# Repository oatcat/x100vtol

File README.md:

# x100vtol
a 100mm 4-rotor small drone using brushed motors, 2s li-po battery, 60mm prop.
One piece PCB-as-chassic, onboard mosfet motor driver, GY-86 as IMU.
Uses taulabs software. Hardware compatible as DISOVERY F4.

## To make one:
Order the PCB from a fab house, buy the necessary parts, solder the PCB.
Connect a S.BUS reciever to the port and fix the reciever on the PCB.
Flash taulabs firmware using ST-LINK, configure the UAV.

## BOM

Apart from the PCB BOM, you will need to secure the motors onto the PCB.
The motor mount I used is bought on taobao.com. If you can't get one you can change the PCB to suit your motor mount.

A small FPV Camera with built in VTX is needed if FPV is desireable.

A ~550mAh 2S battery is needed, and you will need a strap to fix the battery.
There are 2 slots on the PCB you can use to strap the battery.

For proper takeoff and landing you will need some kind of landing gear.
Just glue a small piece of plastic under each motor mount will be fine.

To flash the STM32 you will need ST-Link. Either a standalone one or a builtin on the Discovery board will be fine.

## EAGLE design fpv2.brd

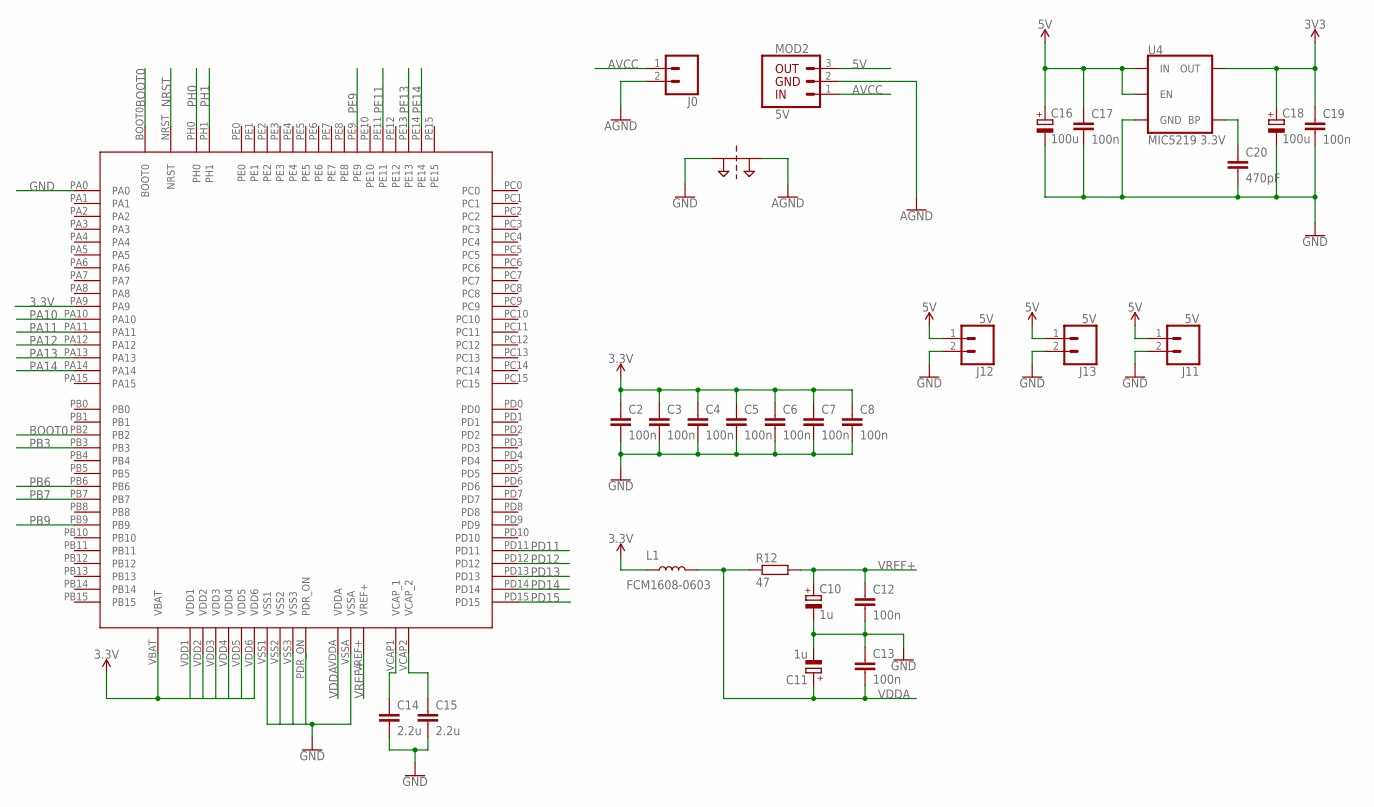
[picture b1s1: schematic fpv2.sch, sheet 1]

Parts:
C2, C3, C4, C5, C6, C7, C8, C12, C13, C17, C19: 100n; C0603
C10, C11: 1u; A/3216-18R
C14, C15: 2.2u; C1206
C16, C18: 100u; SMC_B
C20: 470pF; C0603
J0: CONN_02LOCK_LONGPADS; 1X02_LOCK_LONGPADS
J11, J12, J13: 5V; SMD
L1: FCM1608-0603; 0603
MOD2: 5V; 1X03
R12: 47; R0603
SUPPLY1: 2PT_GND_TIE
U1: STM32F407VGT6; LQFP100
U4: MIC5219 3.3V; SOT23-5

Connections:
3.3V: C2.1, C3.1, C4.1, C5.1, C6.1, C7.1, C8.1, C18.+, C19.1, L1.1, U1.PA9, U1.VBAT, U1.VDD1, U1.VDD2, U1.VDD3, U1.VDD4, U1.VDD5, U1.VDD6, U4.5 (OUT); also elsewhere on the board
5V: C16.+, C17.1, J11.1, J12.1, J13.1, MOD2.3, U4.1 (IN), U4.3 (EN); also elsewhere on the board
AGND: J0.2, MOD2.2, SUPPLY1.P$2; also elsewhere on the board
AVCC: J0.1, MOD2.1; also elsewhere on the board
BOOT0: U1.BOOT0, U1.PB2; also elsewhere on the board
GND: C2.2, C3.2, C4.2, C5.2, C6.2, C7.2, C8.2, C10.-, C11.-, C12.2, C13.1, C14.2, C15.2, C16.-, C17.2, C18.-, C19.2, C20.2, J11.2, J12.2, J13.2, SUPPLY1.P$1, U1.PA0, U1.PDR_ON, U1.VSS1, U1.VSS2, U1.VSS3, U1.VSSA, U4.2 (GND); also elsewhere on the board
unnamed: C14.1, U1.VCAP1 (VCAP_1)
unnamed: C15.1, U1.VCAP2 (VCAP_2)
unnamed: C20.1, U4.4 (BP)
NRST: U1.NRST; also elsewhere on the board
PA10: U1.PA10
PA11: U1.PA11; also elsewhere on the board
PA12: U1.PA12; also elsewhere on the board
PA13: U1.PA13; also elsewhere on the board
PA14: U1.PA14; also elsewhere on the board
PB3: U1.PB3; also elsewhere on the board
PB6: U1.PB6; also elsewhere on the board
PB7: U1.PB7; also elsewhere on the board
PB9: U1.PB9; also elsewhere on the board
PD11: U1.PD11; also elsewhere on the board
PD12: U1.PD12; also elsewhere on the board
PD13: U1.PD13; also elsewhere on the board
PD14: U1.PD14; also elsewhere on the board
PD15: U1.PD15; also elsewhere on the board
PE9: U1.PE9; also elsewhere on the board
PE11: U1.PE11; also elsewhere on the board
PE13: U1.PE13; also elsewhere on the board
PE14: U1.PE14; also elsewhere on the board
PH0: U1.PH0; also elsewhere on the board
PH1: U1.PH1; also elsewhere on the board
VDDA: C11.+, C13.2, L1.2, R12.1, U1.VDDA
VREF+: C10.+, C12.1, R12.2, U1.VREF+

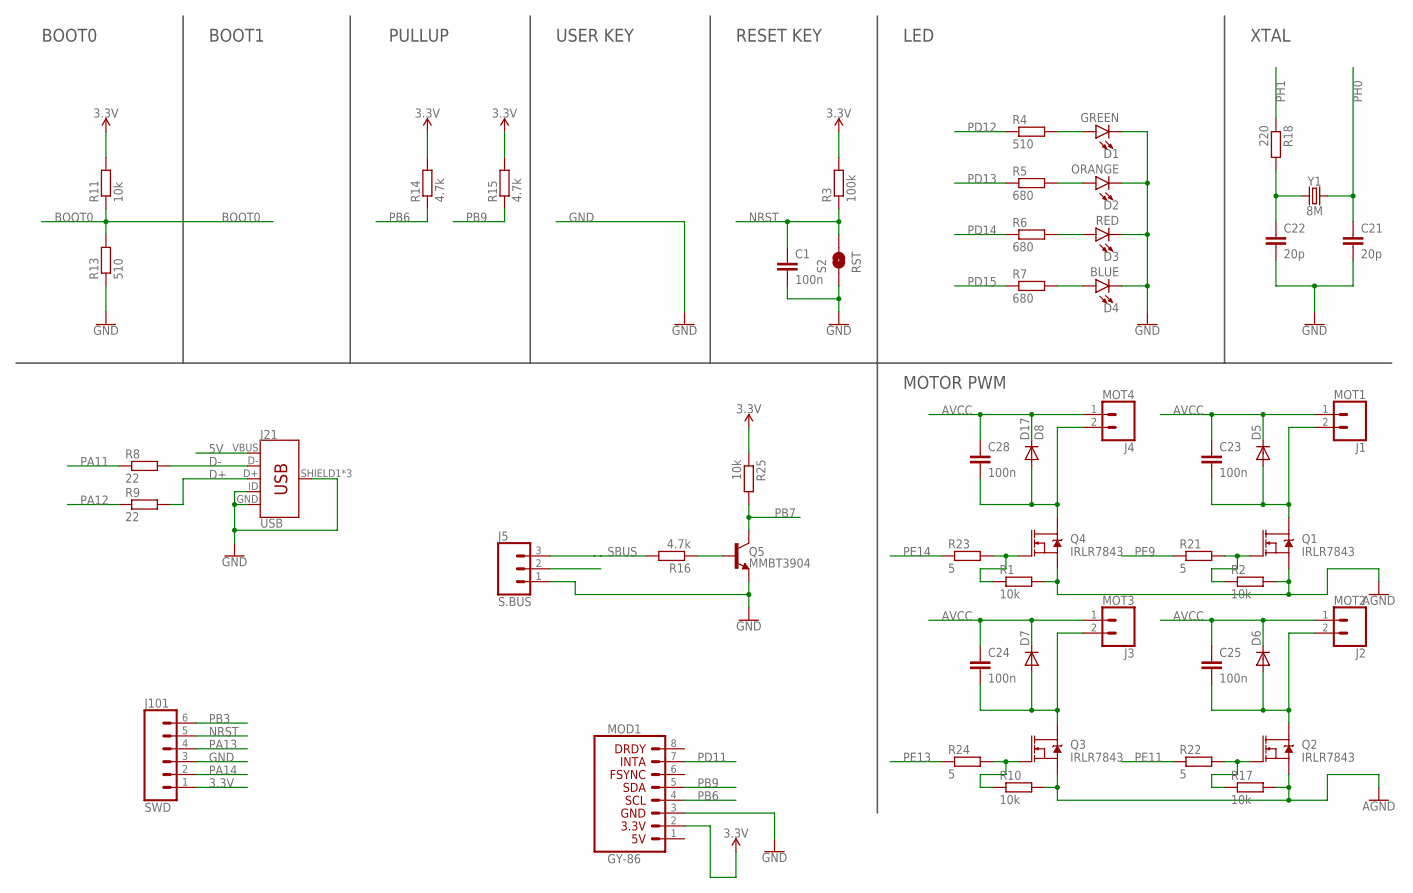
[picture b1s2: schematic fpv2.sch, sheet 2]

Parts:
C1, C23, C24, C25, C28: 100n; C0603
C21, C22: 20p; C0603
D1: GREEN; LED-0603
D2: ORANGE; LED-0603
D3: RED; LED-0603
D4: BLUE; LED-0603
D5, D6, D7: DIODE-DO214AC; DO214AC
D17: D8; DO214AC
J1: MOT1; 1X02_LOCK_LONGPADS
J2: MOT2; 1X02_LOCK_LONGPADS
J3: MOT3; 1X02_LOCK_LONGPADS
J4: MOT4; 1X02_LOCK_LONGPADS
J5: S.BUS; 1X03
J21: USB; USB-B-MICRO-SMD
J101: SWD; 1X06-SMD-FEMALE
MOD1: GY-86
Q1, Q2, Q3, Q4: IRLR7843; DPAK
Q5: MMBT3904; SOT23-3
R1, R2, R10, R11, R17, R25: 10k; R0603
R3: 100k; R0603
R4, R13: 510; R0603
R5, R6, R7: 680; R0603
R8, R9: 22; R0603
R14, R15, R16: 4.7k; R0603
R18: 220; R0603
R21, R22, R23, R24: 5; R0603
S2: RST; SMT-JUMPER_2_NO_NO-SILK
Y1: 8M; CRYSTAL-SMD-5X3.2-2PAD

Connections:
3.3V: J101.1, MOD1.2 (3.3V), R3.2, R11.2, R14.2, R15.2, R25.1; also elsewhere on the board
5V: J5.2, J21.VBUS; also elsewhere on the board
AGND: Q1.3 (S), Q2.3 (S), Q3.3 (S), Q4.3 (S), R1.2, R2.2, R10.2, R17.2; also elsewhere on the board
AVCC: C23.1, C24.1, C25.1, C28.1, D5.C, D6.C, D7.C, D17.C, J1.1, J2.1, J3.1, J4.1; also elsewhere on the board
BOOT0: R11.1, R13.2; also elsewhere on the board
D+: J21.D+, R9.2
D-: J21.D-, R8.2
GND: C1.2, C21.2, C22.2, D1.C, D2.C, D3.C, D4.C, J5.1, J21.GND, J21.ID, J21.SHIELD1 (SHIELD), J21.SHIELD2 (SHIELD), J21.SHIELD3 (SHIELD), J101.3, MOD1.3 (GND), Q5.2 (E), R13.1, S2.1; also elsewhere on the board
unnamed: C23.2, D5.A, J1.2, Q1.4 (D)
unnamed: D1.A, R4.2
unnamed: D2.A, R5.2
unnamed: D3.A, R6.2
unnamed: D4.A, R7.2
unnamed: C25.2, D6.A, J2.2, Q2.4 (D)
unnamed: Q4.1 (G), R1.1, R23.2
unnamed: Q1.1 (G), R2.1, R21.2
unnamed: C22.1, R18.2, Y1.P$1 (1)
unnamed: Q3.1 (G), R10.1, R24.2
unnamed: C28.2, D17.A, J4.2, Q4.4 (D)
unnamed: Q2.1 (G), R17.1, R22.2
unnamed: Q5.1 (B), R16.1
unnamed: C24.2, D7.A, J3.2, Q3.4 (D)
NRST: C1.1, J101.5, R3.1, S2.2; also elsewhere on the board
PA11: R8.1; also elsewhere on the board
PA12: R9.1; also elsewhere on the board
PA13: J101.4; also elsewhere on the board
PA14: J101.2; also elsewhere on the board
PB3: J101.6; also elsewhere on the board
PB6: MOD1.4 (SCL), R14.1; also elsewhere on the board
PB7: Q5.3 (C), R25.2; also elsewhere on the board
PB9: MOD1.5 (SDA), R15.1; also elsewhere on the board
PD11: MOD1.7 (INTA); also elsewhere on the board
PD12: R4.1; also elsewhere on the board
PD13: R5.1; also elsewhere on the board
PD14: R6.1; also elsewhere on the board
PD15: R7.1; also elsewhere on the board
PE9: R21.1; also elsewhere on the board
PE11: R22.1; also elsewhere on the board
PE13: R24.1; also elsewhere on the board
PE14: R23.1; also elsewhere on the board
PH0: C21.1, Y1.P$2 (2); also elsewhere on the board
PH1: R18.1; also elsewhere on the board
SBUS: J5.3, R16.2

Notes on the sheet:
BOOT0
BOOT1
PULLUP
USER KEY
RESET KEY
LED
XTAL
MOTOR PWM

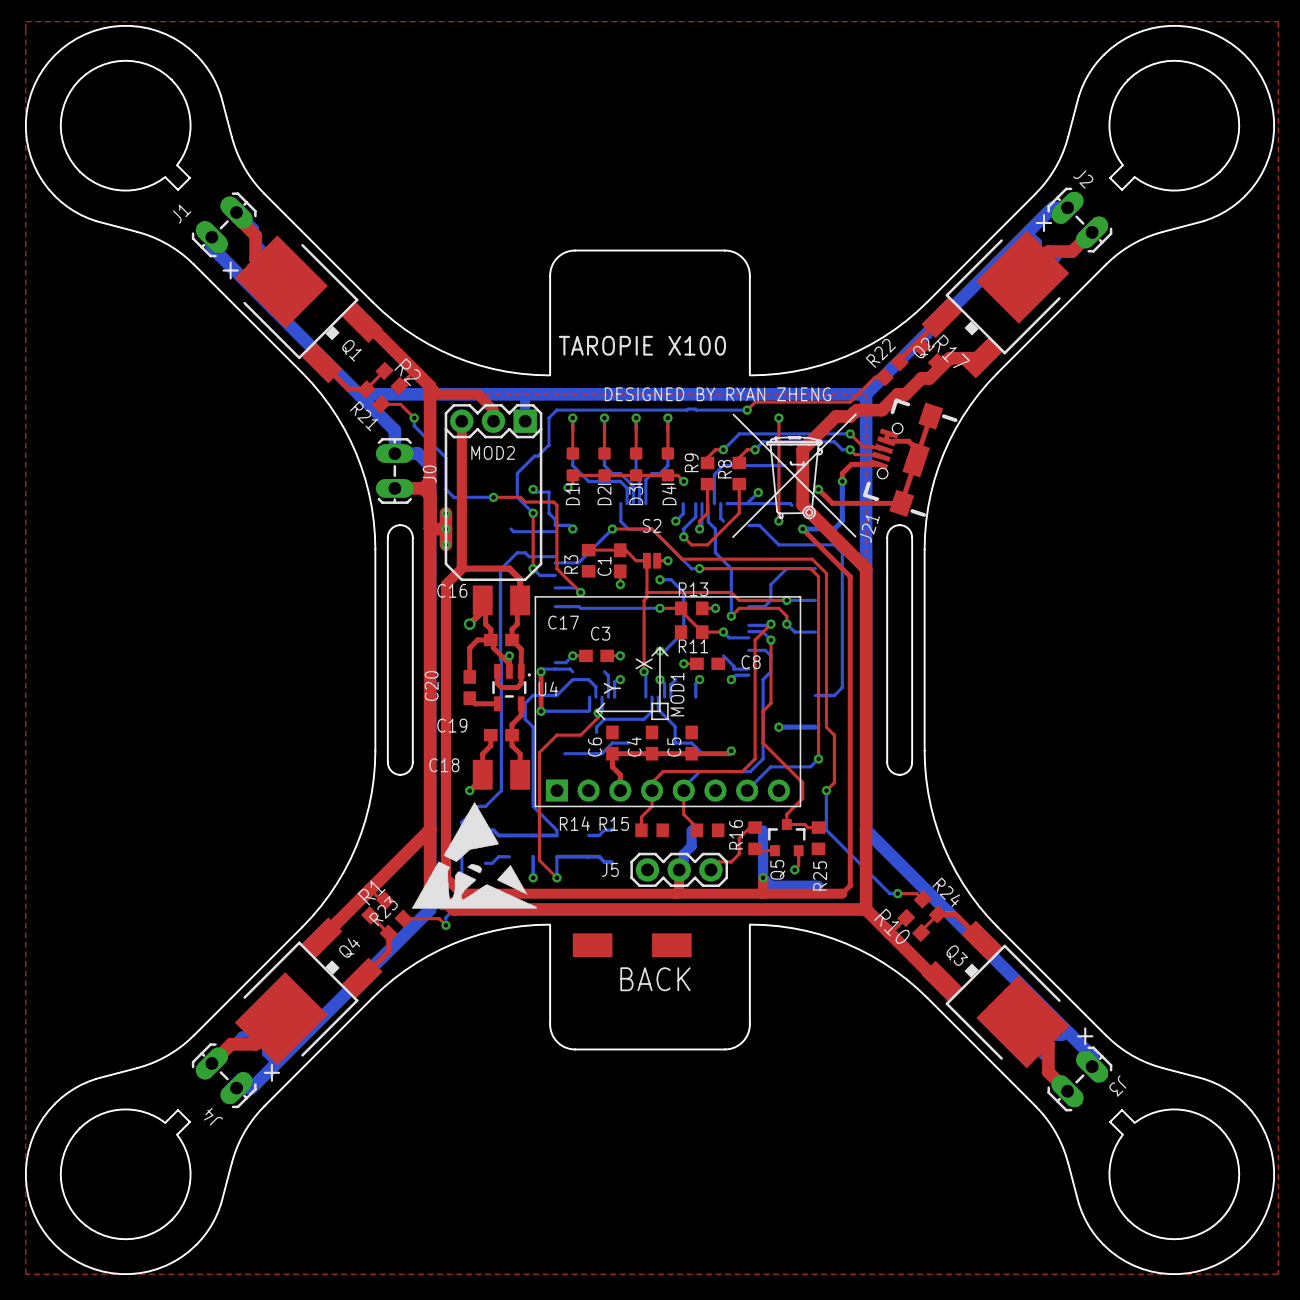
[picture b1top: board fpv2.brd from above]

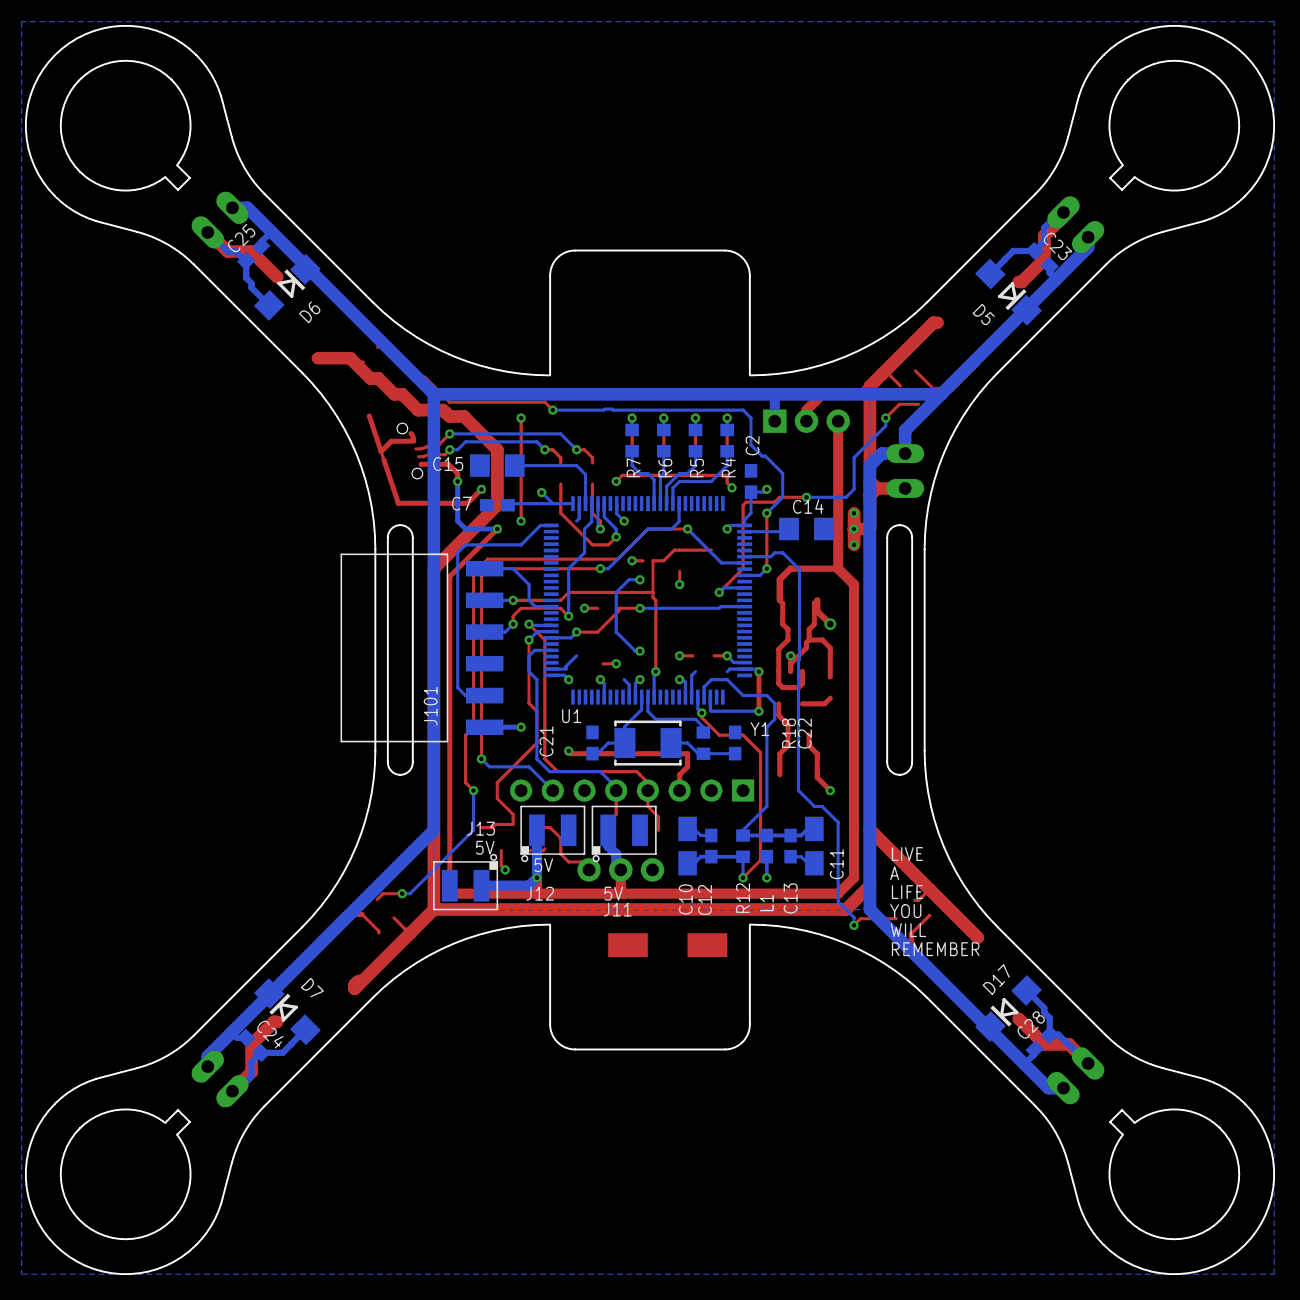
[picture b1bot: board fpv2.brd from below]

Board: 2 copper layers, 100.0 x 100.0 mm, 82 parts (31 on the bottom side), 48 nets.

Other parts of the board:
U$1: TONNE_10.00
U$2: ESD_10.00

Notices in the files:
parts and their libraries:
SparkFun-LED: Licensing: Creative Commons ShareAlike 4.0 International - https://creativecommons.org/licenses/by-sa/4.0
